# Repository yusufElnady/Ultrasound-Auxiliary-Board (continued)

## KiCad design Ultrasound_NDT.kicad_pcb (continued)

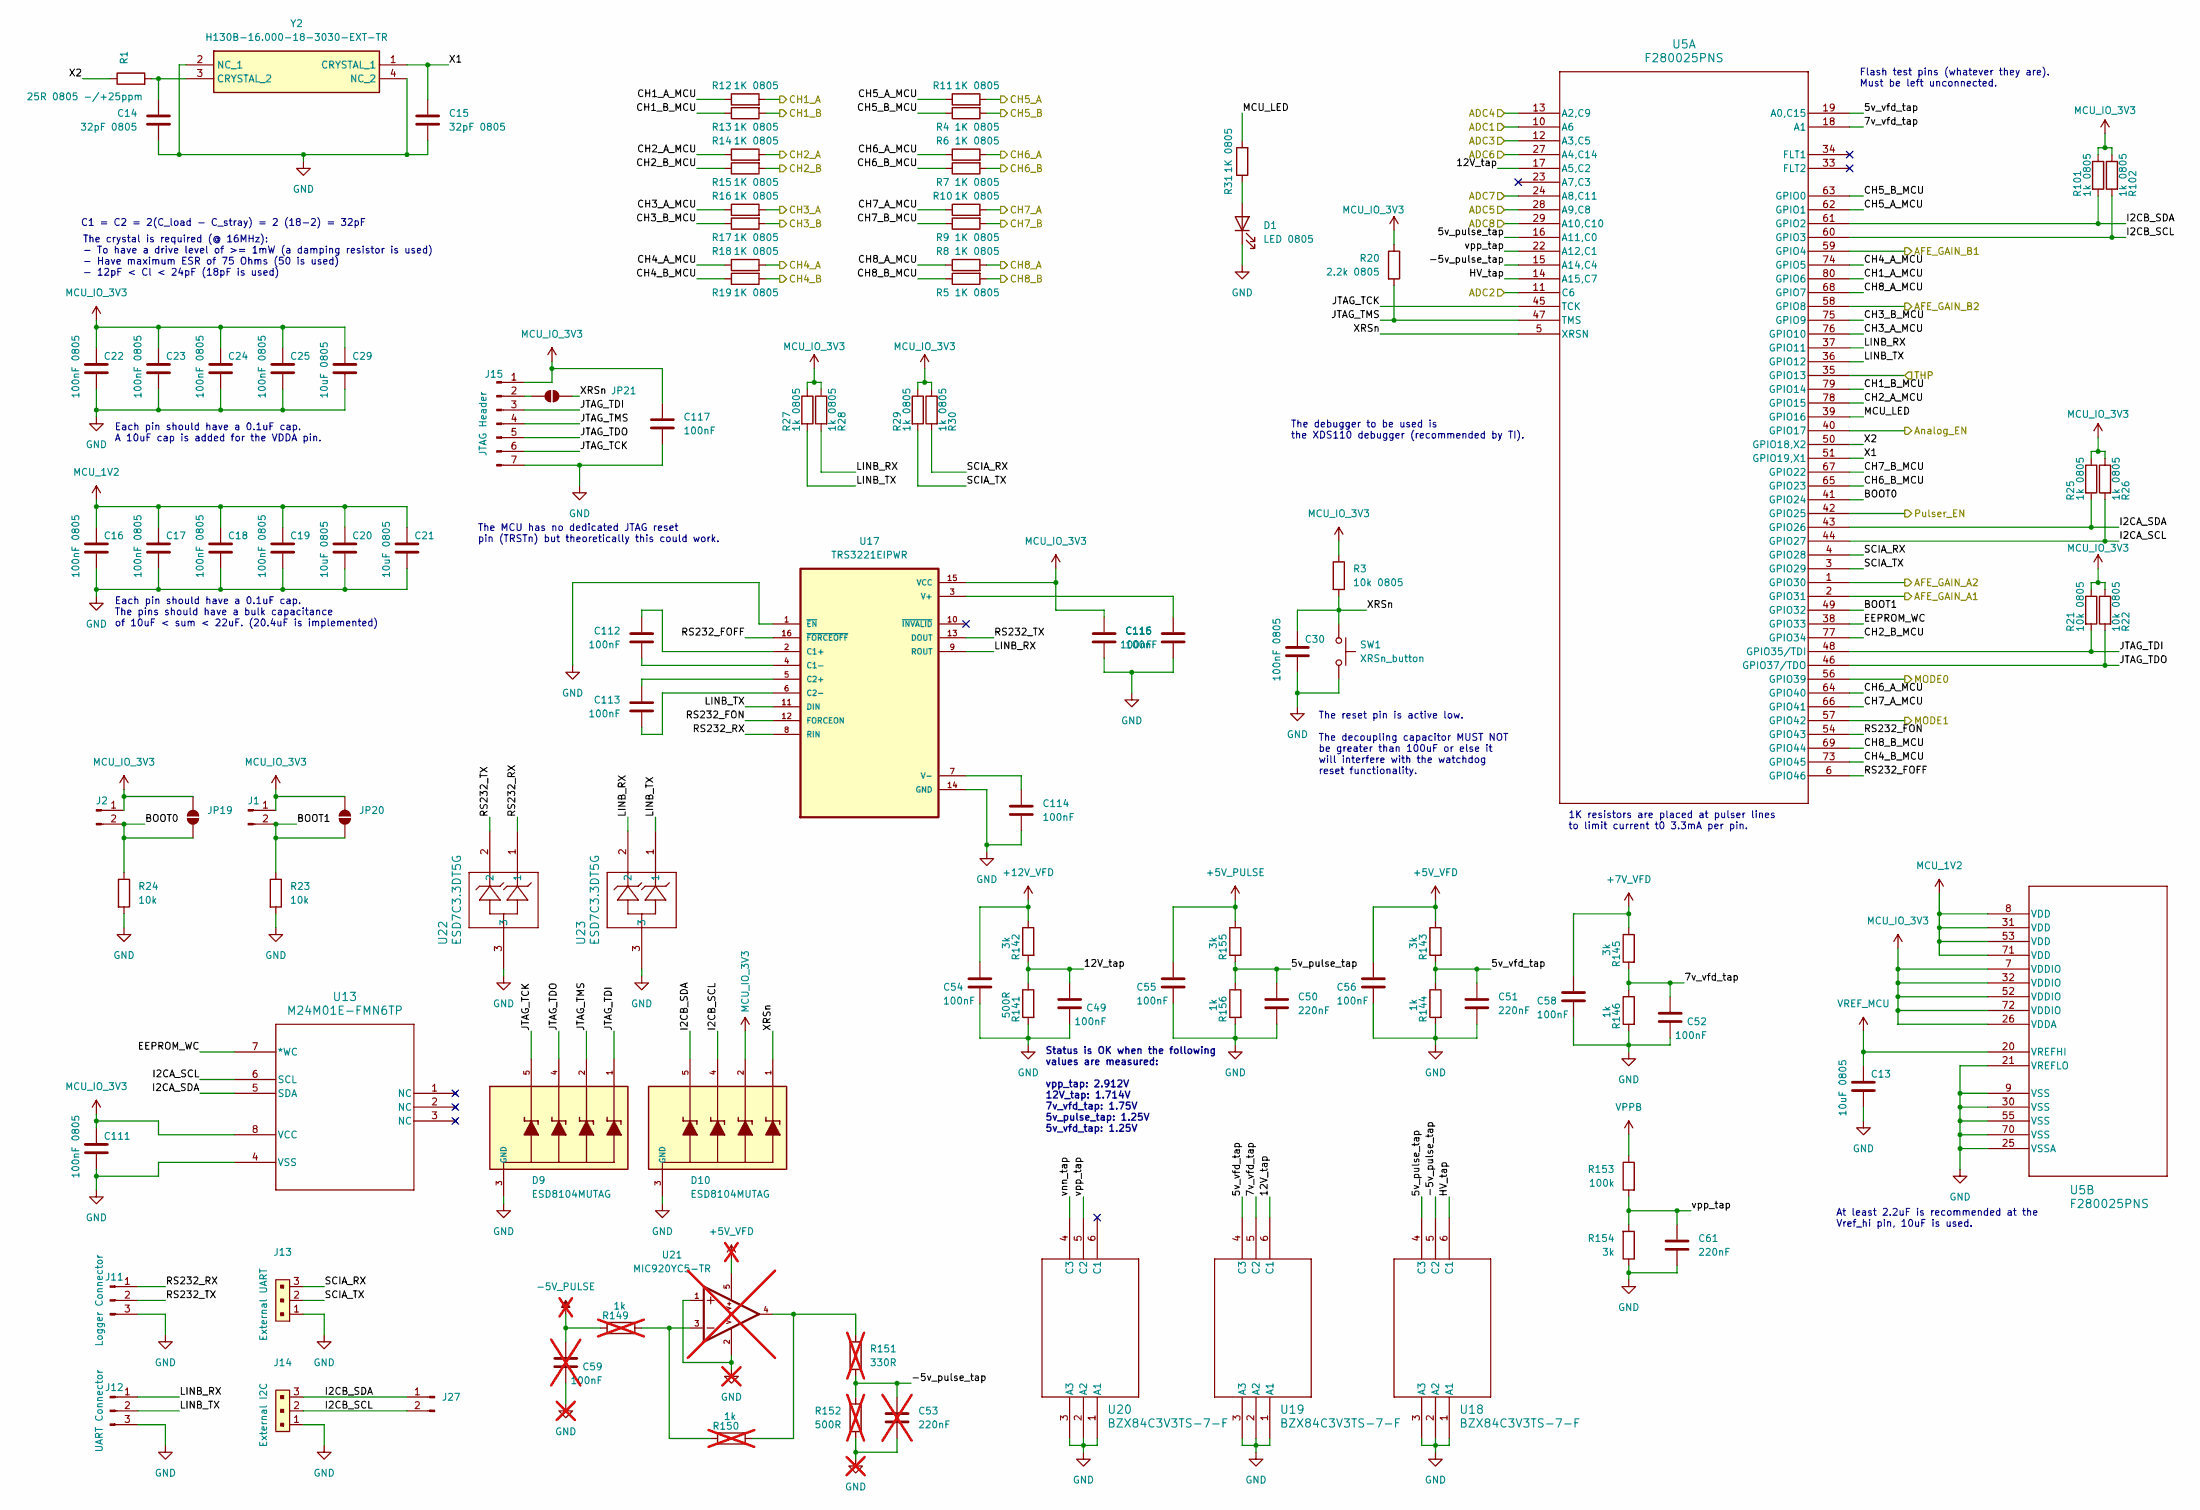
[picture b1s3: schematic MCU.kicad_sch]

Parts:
C13, C20, C21, C29: 10uF 0805; C_0603_1608Metric
C14, C15: 32pF 0805; C_0603_1608Metric
C16, C17, C18, C19, C22, C23, C24, C25, C30, C111: 100nF 0805; C_0603_1608Metric
C49, C52, C54, C55, C56, C58, C112, C113, C114, C115, C116, C117: 100nF; C_0603_1608Metric
C50, C51, C61: 220nF; C_0603_1608Metric
C53: 220nF; C_0603_1608Metric; not fitted
C59: 100nF; C_0603_1608Metric; not fitted
D1: LED 0805; LED_0805_2012Metric
D9, D10: ESD8104MUTAG; DIO_ESD8104MUTAG; PARTREV 8
J1, J2, J27: Conn_01x02_Pin; PinHeader_1x02_P2.54mm_Vertical
J11: Logger Connector; PinHeader_1x03_P2.54mm_Vertical
J12: UART Connector; PinHeader_1x03_P2.54mm_Vertical
J13: External UART; PinHeader_1x3_P2.5mm_Drill1.1mm; MPN B3B-XH-A(LF)(SN); Digi-Key_PN 455-2248-ND
J14: External I2C; PinHeader_1x3_P2.5mm_Drill1.1mm; MPN B3B-XH-A(LF)(SN); Digi-Key_PN 455-2248-ND
J15: JTAG Header; PinHeader_1x07_P2.54mm_Vertical
JP19, JP20, JP21: SolderJumper_2_Open; SolderJumper-2_P1.3mm_Open_Pad1.0x1.5mm
R1: 25R 0805 -/+25ppm; R_0603_1608Metric
R3, R21, R22: 10k 0805; R_0603_1608Metric
R4, R5, R6, R7, R8, R9, R10, R11, R12, R13, R14, R15, R16, R17, R18, R19, R31: 1K 0805; R_0603_1608Metric
R20: 2.2k 0805; R_0603_1608Metric
R23, R24: 10k; R_0603_1608Metric
R25, R26, R27, R28, R29, R30, R101, R102: 1k 0805; R_0603_1608Metric
R141: 500R; R_0603_1608Metric
R142, R143, R145, R154, R155: 3k; R_0603_1608Metric
R144, R146, R156: 1k; R_0603_1608Metric
R149, R150: 1k; R_0603_1608Metric; not fitted
R151: 330R; R_0603_1608Metric; not fitted
R152: 500R; R_0603_1608Metric; not fitted
R153: 100k; R_0603_1608Metric
SW1: XRSn_button; SW_Push_SPST_NO_Alps_SKRK
U5: F280025PNS; PQFP_025PNSR_TEX
U13: M24M01E-FMN6TP; SO8N_4X5X1P27_STM
U17: TRS3221EIPWR; SOP65P640X120-16N
U18, U19, U20: BZX84C3V3TS-7-F; SOT-363_DIO
U21: MIC920YC5-TR; SOT65P210X110-5N; PARTREV March 2006; not fitted
U22, U23: ESD7C3.3DT5G; SOT_C3.3DT5G_ONS
Y2: H130B-16.000-18-3030-EXT-TR; H130B16000183030EXTTR; Manufacturer_Part_Number H130B-16.000-18-3030-EXT-TR

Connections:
+5V_PULSE: C55.1, R155.1; also elsewhere on the board
+5V_VFD: C56.1, R143.1, U21.5; also elsewhere on the board
+7V_VFD: C58.1, R145.1; also elsewhere on the board
+12V_VFD: C54.1, R142.1; also elsewhere on the board
/Main MCU Section/5v_pulse_tap: C50.1, R155.2, R156.1, U5.16 (A11,C0), U18.4 (C3)
/Main MCU Section/5v_vfd_tap: C51.1, R143.2, R144.1, U5.19 (A0,C15), U19.4 (C3)
/Main MCU Section/7v_vfd_tap: C52.1, R145.2, R146.1, U5.18 (A1), U19.5 (C2)
/Main MCU Section/12V_tap: C49.1, R141.1, R142.2, U5.17 (A5,C2), U19.6 (C1)
/Main MCU Section/-5v_pulse_tap: C53.1, R151.1, R152.2, U5.15 (A14,C4), U18.5 (C2)
/Main MCU Section/ADC1: U5.10 (A6); also elsewhere on the board
/Main MCU Section/ADC2: U5.11 (C6); also elsewhere on the board
/Main MCU Section/ADC3: U5.12 (A3,C5); also elsewhere on the board
/Main MCU Section/ADC4: U5.13 (A2,C9); also elsewhere on the board
/Main MCU Section/ADC5: U5.28 (A9,C8); also elsewhere on the board
/Main MCU Section/ADC6: U5.27 (A4,C14); also elsewhere on the board
/Main MCU Section/ADC7: U5.24 (A8,C11); also elsewhere on the board
/Main MCU Section/ADC8: U5.29 (A10,C10); also elsewhere on the board
/Main MCU Section/AFE_GAIN_A1: U5.2 (GPIO31); also elsewhere on the board
/Main MCU Section/AFE_GAIN_A2: U5.1 (GPIO30); also elsewhere on the board
/Main MCU Section/AFE_GAIN_B1: U5.59 (GPIO4); also elsewhere on the board
/Main MCU Section/AFE_GAIN_B2: U5.58 (GPIO8); also elsewhere on the board
/Main MCU Section/Analog_EN: U5.40 (GPIO17); also elsewhere on the board
/Main MCU Section/BOOT0: J2.2, JP19.1 (A), R24.1, U5.41 (GPIO24)
/Main MCU Section/BOOT1: J1.2, JP20.1 (A), R23.1, U5.49 (GPIO32)
/Main MCU Section/CH1_A: R12.2; also elsewhere on the board
/Main MCU Section/CH1_A_MCU: R12.1, U5.80 (GPIO6)
/Main MCU Section/CH1_B: R13.2; also elsewhere on the board
/Main MCU Section/CH1_B_MCU: R13.1, U5.79 (GPIO14)
/Main MCU Section/CH2_A: R14.2; also elsewhere on the board
/Main MCU Section/CH2_A_MCU: R14.1, U5.78 (GPIO15)
/Main MCU Section/CH2_B: R15.2; also elsewhere on the board
/Main MCU Section/CH2_B_MCU: R15.1, U5.77 (GPIO34)
/Main MCU Section/CH3_A: R16.2; also elsewhere on the board
/Main MCU Section/CH3_A_MCU: R16.1, U5.76 (GPIO10)
/Main MCU Section/CH3_B: R17.2; also elsewhere on the board
/Main MCU Section/CH3_B_MCU: R17.1, U5.75 (GPIO9)
/Main MCU Section/CH4_A: R18.2; also elsewhere on the board
/Main MCU Section/CH4_A_MCU: R18.1, U5.74 (GPIO5)
/Main MCU Section/CH4_B: R19.2; also elsewhere on the board
/Main MCU Section/CH4_B_MCU: R19.1, U5.73 (GPIO45)
/Main MCU Section/CH5_A: R11.2; also elsewhere on the board
/Main MCU Section/CH5_A_MCU: R11.1, U5.62 (GPIO1)
/Main MCU Section/CH5_B: R4.2; also elsewhere on the board
/Main MCU Section/CH5_B_MCU: R4.1, U5.63 (GPIO0)
/Main MCU Section/CH6_A: R6.2; also elsewhere on the board
/Main MCU Section/CH6_A_MCU: R6.1, U5.64 (GPIO40)
/Main MCU Section/CH6_B: R7.2; also elsewhere on the board
/Main MCU Section/CH6_B_MCU: R7.1, U5.65 (GPIO23)
/Main MCU Section/CH7_A: R10.2; also elsewhere on the board
/Main MCU Section/CH7_A_MCU: R10.1, U5.66 (GPIO41)
/Main MCU Section/CH7_B: R9.2; also elsewhere on the board
/Main MCU Section/CH7_B_MCU: R9.1, U5.67 (GPIO22)
/Main MCU Section/CH8_A: R8.2; also elsewhere on the board
/Main MCU Section/CH8_A_MCU: R8.1, U5.68 (GPIO7)
/Main MCU Section/CH8_B: R5.2; also elsewhere on the board
/Main MCU Section/CH8_B_MCU: R5.1, U5.69 (GPIO44)
/Main MCU Section/EEPROM_WC: U5.38 (GPIO33), U13.7 (*WC)
/Main MCU Section/HV_tap: U5.14 (A15,C7), U18.6 (C1)
/Main MCU Section/I2CA_SCL: R26.2, U5.44 (GPIO27), U13.6 (SCL)
/Main MCU Section/I2CA_SDA: R25.2, U5.43 (GPIO26), U13.5 (SDA)
/Main MCU Section/I2CB_SCL: D10.4, J14.2, J27.2, R102.2, U5.60 (GPIO3)
/Main MCU Section/I2CB_SDA: D10.5, J14.3, J27.1, R101.2, U5.61 (GPIO2)
/Main MCU Section/JTAG_TCK: D9.5, J15.6, U5.45 (TCK)
/Main MCU Section/JTAG_TDI: D9.1, J15.3, R21.2, U5.48 (GPIO35/TDI)
/Main MCU Section/JTAG_TDO: D9.4, J15.5, R22.2, U5.46 (GPIO37/TDO)
/Main MCU Section/JTAG_TMS: D9.2, J15.4, R20.2, U5.47 (TMS)
/Main MCU Section/LINB_RX: J12.1, R28.2, U5.37 (GPIO11), U17.9 (ROUT), U23.2
/Main MCU Section/LINB_TX: J12.2, R27.2, U5.36 (GPIO12), U17.11 (DIN), U23.1
/Main MCU Section/MCU_LED: R31.2, U5.39 (GPIO16)
/Main MCU Section/MODE0: U5.56 (GPIO39); also elsewhere on the board
/Main MCU Section/MODE1: U5.57 (GPIO42); also elsewhere on the board
/Main MCU Section/Pulser_EN: U5.42 (GPIO25); also elsewhere on the board
/Main MCU Section/RS232_FOFF: U5.6 (GPIO46), U17.16 (~FORCEOFF)
/Main MCU Section/RS232_FON: U5.54 (GPIO43), U17.12 (FORCEON)
/Main MCU Section/RS232_RX: J11.1, U17.8 (RIN), U22.1
/Main MCU Section/RS232_TX: J11.2, U17.13 (DOUT), U22.2
/Main MCU Section/SCIA_RX: J13.3, R30.2, U5.4 (GPIO28)
/Main MCU Section/SCIA_TX: J13.2, R29.2, U5.3 (GPIO29)
/Main MCU Section/THP: U5.35 (GPIO13); also elsewhere on the board
/Main MCU Section/X1: C15.1, U5.51 (GPIO19,X1), Y2.1 (CRYSTAL_1)
/Main MCU Section/X2: R1.1, U5.50 (GPIO18,X2)
/Main MCU Section/XRSn: C30.1, D10.1, JP21.2 (B), R3.2, SW1.1, U5.5 (XRSN)
/Main MCU Section/vnn_tap: U20.4 (C3)
/Main MCU Section/vpp_tap: C61.1, R153.2, R154.2, U5.22 (A12,C1), U20.5 (C2)
GND: C13.2, C14.2, C15.2, C16.2, C17.2, C18.2, C19.2, C20.2, C21.2, C22.2, C23.2, C24.2, C25.2, C29.2, C30.2, C49.2, C50.2, C51.2, C52.2, C53.2, C54.2, C55.2, C56.2, C58.2, C59.2, C61.2, C111.2, C114.2, C115.2, C116.2, C117.2, D1.1 (K), D9.3 (GND), D9.8 (GND), D10.3 (GND), D10.8 (GND), J11.3, J12.3, J13.1, J14.1, J15.7, R23.2, R24.2, R141.2, R144.2, R146.2, R152.1, R154.1, R156.2, SW1.2, U5.9 (VSS), U5.21 (VREFLO), U5.25 (VSSA), U5.30 (VSS), U5.55 (VSS), U5.70 (VSS), U13.4 (VSS), U17.1 (~EN), U17.14 (GND), U18.1 (A1), U18.2 (A2), U18.3 (A3), U19.1 (A1), U19.2 (A2), U19.3 (A3), U20.1 (A1), U20.2 (A2), U20.3 (A3), U21.1, U21.2, U22.3, U23.3, Y2.2 (NC_1), Y2.4 (NC_2); also elsewhere on the board
MCU_1V2: C16.1, C17.1, C18.1, C19.1, C20.1, C21.1, U5.8 (VDD), U5.31 (VDD), U5.53 (VDD), U5.71 (VDD)
MCU_IO_3V3: C22.1, C23.1, C24.1, C25.1, C29.1, C111.1, C116.1, C117.1, D10.2, J1.1, J2.1, J15.1, JP19.2 (B), JP20.2 (B), R3.1, R20.1, R21.1, R22.1, R25.1, R26.1, R27.1, R28.1, R29.1, R30.1, R101.1, R102.1, U5.7 (VDDIO), U5.26 (VDDA), U5.32 (VDDIO), U5.52 (VDDIO), U5.72 (VDDIO), U13.8 (VCC), U17.15 (VCC); also elsewhere on the board
unnamed: C59.1, R149.2
unnamed: D1.2 (A), R31.1
unnamed: J15.2, JP21.1 (A)
unnamed: R149.1, R150.2, U21.3
unnamed: R150.1, R151.2, U21.4
unnamed: C112.1, U17.2 (C1+)
unnamed: C112.2, U17.4 (C1-)
unnamed: C113.1, U17.5 (C2+)
unnamed: C113.2, U17.6 (C2-)
unnamed: C115.1, U17.3 (V+)
unnamed: C114.1, U17.7 (V-)
unnamed: C14.1, R1.2, Y2.3 (CRYSTAL_2)
VPPB: R153.1; also elsewhere on the board
VREF_MCU: C13.1, U5.20 (VREFHI); also elsewhere on the board

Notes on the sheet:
Status is OK when the following values are measured: vpp_tap: 2.912V 12V_tap: 1.714V 7v_vfd_tap: 1.75V 5v_pulse_tap: 1.25V 5v_vfd_tap: 1.25V
The crystal is required (@ 16MHz): - To have a drive level of >= 1mW (a damping resistor is used) - Have maximum ESR of 75 Ohms (50 is used) - 12pF < Cl < 24pF (18pF is used)
Each pin should have a 0.1uF cap. The pins should have a bulk capacitance of 10uF < sum < 22uF. (20.4uF is implemented)
Each pin should have a 0.1uF cap. A 10uF cap is added for the VDDA pin.
The debugger to be used is the XDS110 debugger (recommended by TI).
The MCU has no dedicated JTAG reset pin (TRSTn) but theoretically this could work.
At least 2.2uF is recommended at the Vref_hi pin, 10uF is used.
1K resistors are placed at pulser lines to limit current t0 3.3mA per pin.
The reset pin is active low. The decoupling capacitor MUST NOT be greater than 100uF or else it will interfere with the watchdog reset functionality.
Flash test pins (whatever they are). Must be left unconnected.
C1 = C2 = 2(C_load - C_stray) = 2 (18-2) = 32pF

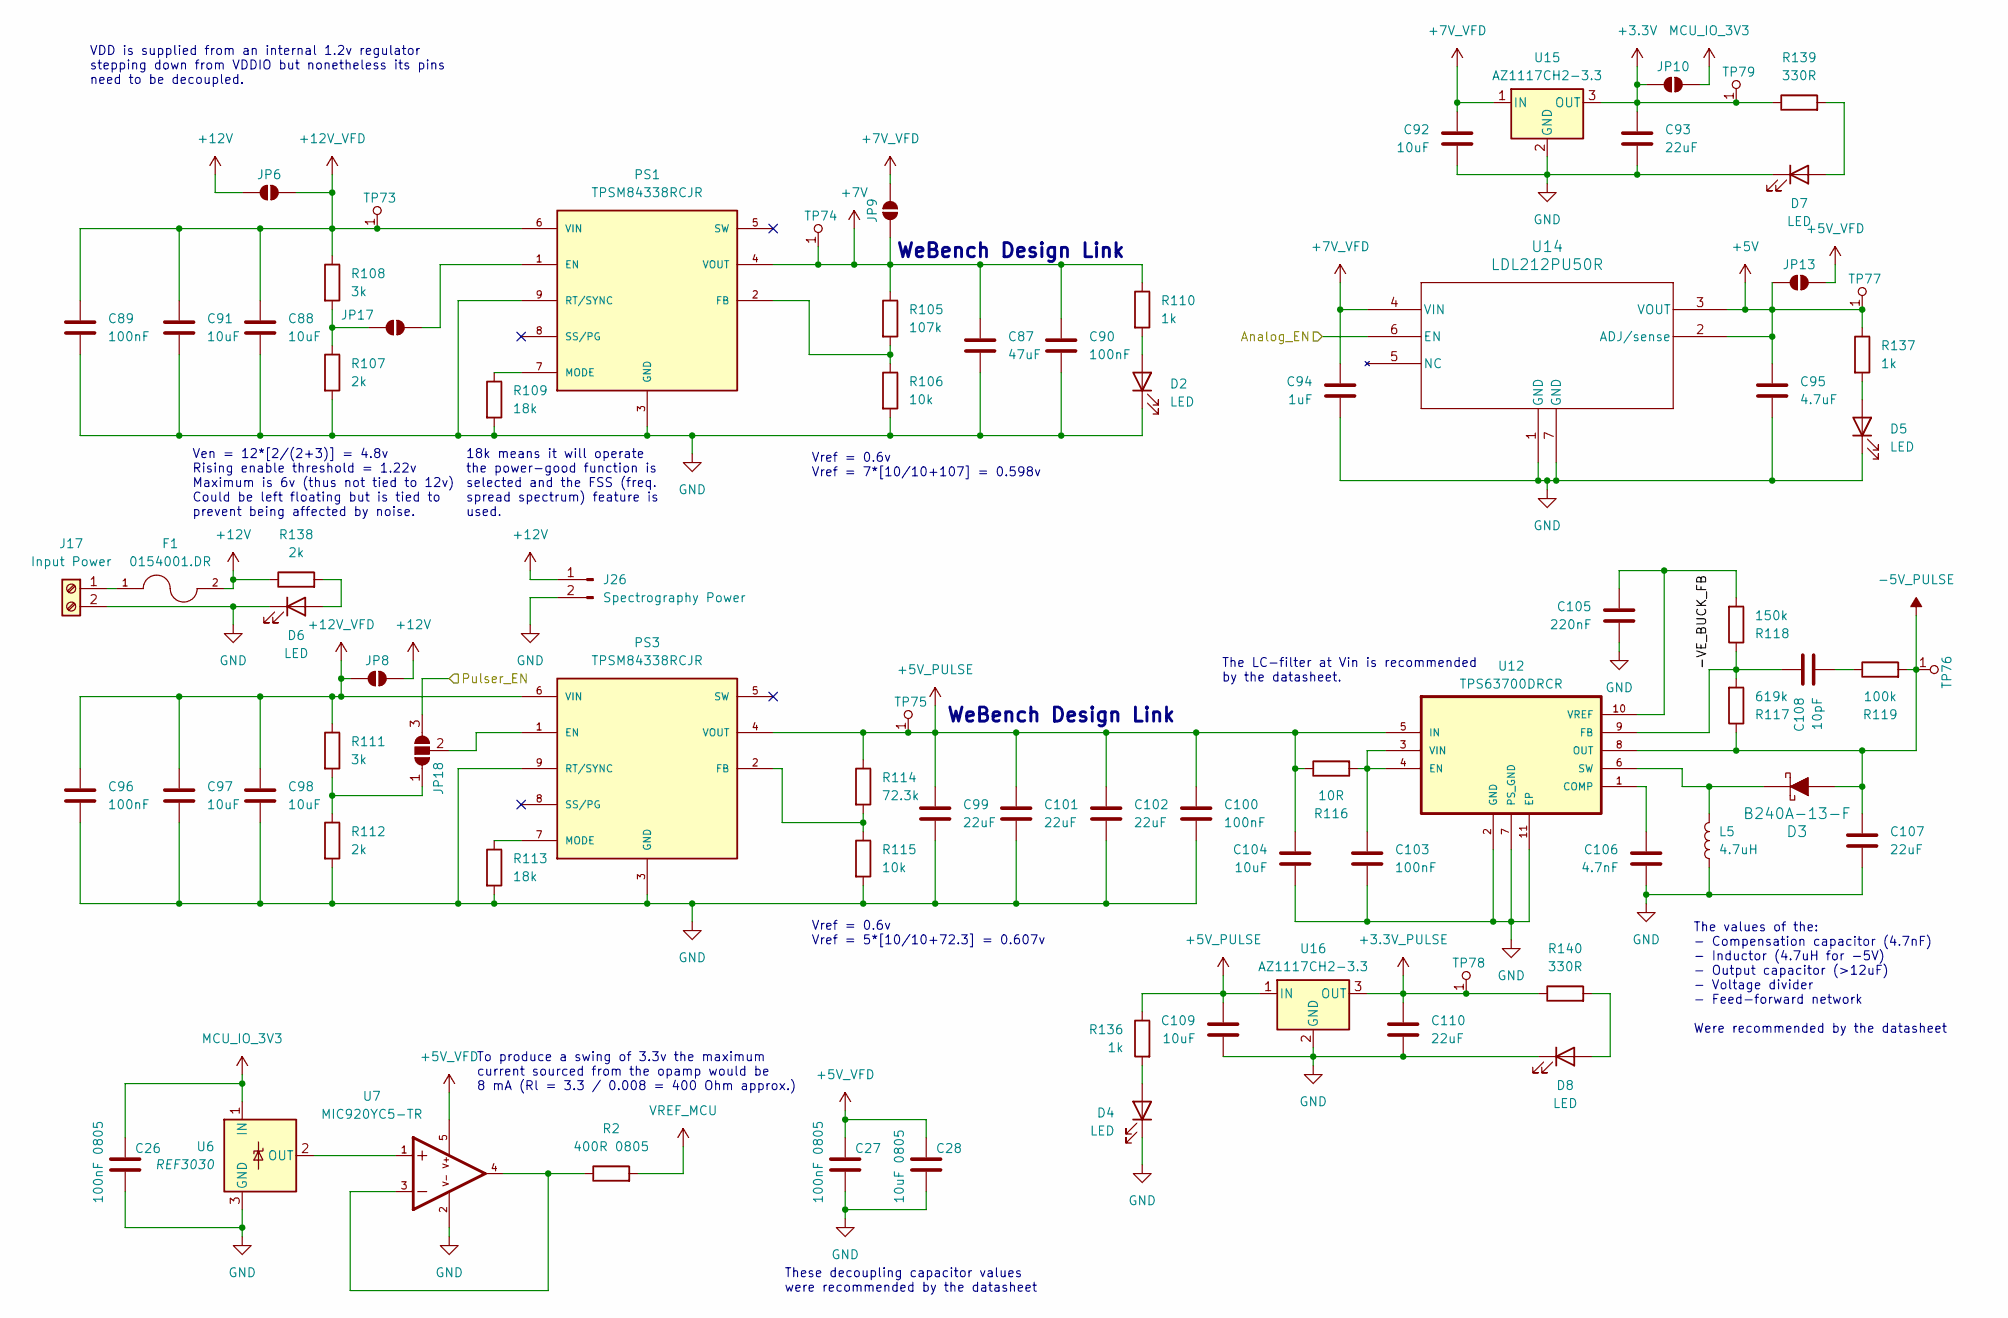
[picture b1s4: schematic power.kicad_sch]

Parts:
C26, C27: 100nF 0805; C_0603_1608Metric
C28: 10uF 0805; C_0603_1608Metric
C87: 47uF; C_1210_3225Metric
C88, C91, C92, C97, C98, C104, C109: 10uF; C_0805_2012Metric
C89, C90, C96, C100, C103: 100nF; C_0603_1608Metric
C93, C99, C101, C102, C107, C110: 22uF; C_0805_2012Metric
C94: 1uF; C_0603_1608Metric
C95: 4.7uF; C_0805_2012Metric
C105: 220nF; C_0603_1608Metric
C106: 4.7nF; C_0603_1608Metric
C108: 10pF; C_0603_1608Metric
D2, D4, D5, D6, D7, D8: LED; LED_0805_2012Metric
D3: B240A-13-F; DO-214AC; MPN B240A-13-F; Digi-Key_PN B240A-FDICT-ND
F1: 0154001.DR; FUSE_0154001.DR; PARTREV GD
J17: Input Power; TerminalBlock_MaiXu_MX126-5.0-02P_1x02_P5.00mm
J26: Spectrography Power; PinHeader_1x02_P2.54mm_Vertical
JP6, JP8, JP9, JP10, JP13: SolderJumper_2_Open; SolderJumper-2_P1.3mm_Open_RoundedPad1.0x1.5mm
JP17: SolderJumper_2_Open; SolderJumper-2_P1.3mm_Open_Pad1.0x1.5mm
JP18: SolderJumper_3_Open; SolderJumper-3_P1.3mm_Open_Pad1.0x1.5mm
L5: 4.7uH; L_0805_2012Metric
PS1, PS3: TPSM84338RCJR; CONV_TPSM84338RCJR; PARTREV November 2024
R2: 400R 0805; R_0603_1608Metric
R105: 107k; R_0603_1608Metric
R106, R115: 10k; R_0603_1608Metric
R107, R112, R138: 2k; R_0603_1608Metric
R108, R111: 3k; R_0603_1608Metric
R109, R113: 18k; R_0603_1608Metric
R110, R136, R137: 1k; R_0603_1608Metric
R114: 72.3k; R_0603_1608Metric
R116: 10R; R_0603_1608Metric
R117: 619k; R_0603_1608Metric
R118: 150k; R_0603_1608Metric
R119: 100k; R_0603_1608Metric
R139, R140: 330R; R_0603_1608Metric
TP73, TP74, TP75, TP76, TP77, TP78, TP79: RCT-0C; PROBE_PAD_0805; MPN RCT-0C; Digi-Key_PN A106144CT-ND
U6: REF3030; SOT-23
U7: MIC920YC5-TR; SOT65P210X110-5N; PARTREV March 2006
U12: TPS63700DRCR; VREG_V62_16624-01YE
U14: LDL212PU50R; DFN_2PU50R_STM
U15, U16: AZ1117CH2-3.3; SOT-223-3_TabPin2

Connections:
+3.3V: C93.1, JP10.1 (A), R139.1, TP79.1, U15.3 (OUT)
+3.3V_PULSE: C110.1, R140.1, TP78.1, U16.3 (OUT); also elsewhere on the board
+5V: C95.1, JP13.1 (A), R137.1, TP77.1, U14.2 (ADJ/sense), U14.3 (VOUT)
+5V_PULSE: C99.1, C100.1, C101.1, C102.1, C104.1, C109.1, PS3.4 (VOUT), R114.1, R116.1, R136.1, TP75.1, U12.5 (IN), U16.1 (IN); also elsewhere on the board
+5V_VFD: C27.1, C28.1, JP13.2 (B), U7.5; also elsewhere on the board
+7V: C87.1, C90.1, JP9.1 (A), PS1.4 (VOUT), R105.1, R110.1, TP74.1
+7V_VFD: C92.1, C94.1, JP9.2 (B), U14.4 (VIN), U15.1 (IN); also elsewhere on the board
+12V: F1.2, J26.1, JP6.1 (A), JP8.2 (B), R138.1
+12V_VFD: C88.1, C89.1, C91.1, C96.1, C97.1, C98.1, JP6.2 (B), JP8.1 (A), PS1.6 (VIN), PS3.6 (VIN), R108.1, R111.1, TP73.1; also elsewhere on the board
-5V_PULSE: C107.1, D3.A, R117.1, R119.2, TP76.1, U12.8 (OUT); also elsewhere on the board
/Main MCU Section/Analog_EN: U14.6 (EN); also elsewhere on the board
/Main MCU Section/Pulser_EN: JP18.3 (B); also elsewhere on the board
/Power Section/-VE_BUCK_FB: C108.1, R117.2, R118.1, U12.9 (FB)
GND: C26.2, C27.2, C28.2, C87.2, C88.2, C89.2, C90.2, C91.2, C92.2, C93.2, C94.2, C95.2, C96.2, C97.2, C98.2, C99.2, C100.2, C101.2, C102.2, C103.2, C104.2, C105.2, C106.2, C107.2, C109.2, C110.2, D2.1 (K), D4.1 (K), D5.1 (K), D6.1 (K), D7.1 (K), D8.1 (K), J17.2, J26.2, L5.1, PS1.3 (GND), PS1.9 (RT/SYNC), PS3.3 (GND), PS3.9 (RT/SYNC), R106.2, R107.2, R109.2, R112.2, R113.2, R115.2, U6.3 (GND), U7.2, U12.2 (GND), U12.7 (PS_GND), U12.11 (EP), U14.1 (GND), U14.7 (GND), U15.2 (GND), U16.2 (GND); also elsewhere on the board
MCU_IO_3V3: C26.1, JP10.2 (B), U6.1 (IN); also elsewhere on the board
unnamed: C108.2, R119.1
unnamed: D2.2 (A), R110.2
unnamed: D4.2 (A), R136.2
unnamed: D5.2 (A), R137.2
unnamed: D6.2 (A), R138.2
unnamed: D7.2 (A), R139.2
unnamed: D8.2 (A), R140.2
unnamed: F1.1, J17.1
unnamed: JP17.1 (A), R107.1, R108.2
unnamed: JP17.2 (B), PS1.1 (EN)
unnamed: JP18.1 (A), R111.2, R112.1
unnamed: JP18.2 (C), PS3.1 (EN)
unnamed: PS1.2 (FB), R105.2, R106.1
unnamed: PS1.7 (MODE), R109.1
unnamed: PS3.2 (FB), R114.2, R115.1
unnamed: PS3.7 (MODE), R113.1
unnamed: R2.1, U7.3, U7.4
unnamed: U6.2 (OUT), U7.1
unnamed: C106.1, U12.1 (COMP)
unnamed: C103.1, R116.2, U12.3 (VIN), U12.4 (EN)
unnamed: D3.K, L5.2, U12.6 (SW)
unnamed: C105.1, R118.2, U12.10 (VREF)
VREF_MCU: R2.2; also elsewhere on the board

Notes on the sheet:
Vref = 0.6v Vref = 7*[10/10+107] = 0.598v
18k means it will operate the power-good function is selected and the FSS (freq. spread spectrum) feature is used.
WeBench Design Link
VDD is supplied from an internal 1.2v regulator stepping down from VDDIO but nonetheless its pins need to be decoupled.
Vref = 0.6v Vref = 5*[10/10+72.3] = 0.607v
The values of the: - Compensation capacitor (4.7nF) - Inductor (4.7uH for -5V) - Output capacitor (>12uF) - Voltage divider - Feed-forward network Were recommended by the datasheet
To produce a swing of 3.3v the maximum current sourced from the opamp would be 8 mA (Rl = 3.3 / 0.008 = 400 Ohm approx.)
Ven = 12*[2/(2+3)] = 4.8v Rising enable threshold = 1.22v Maximum is 6v (thus not tied to 12v) Could be left floating but is tied to prevent being affected by noise.
The LC-filter at Vin is recommended by the datasheet.
These decoupling capacitor values were recommended by the datasheet

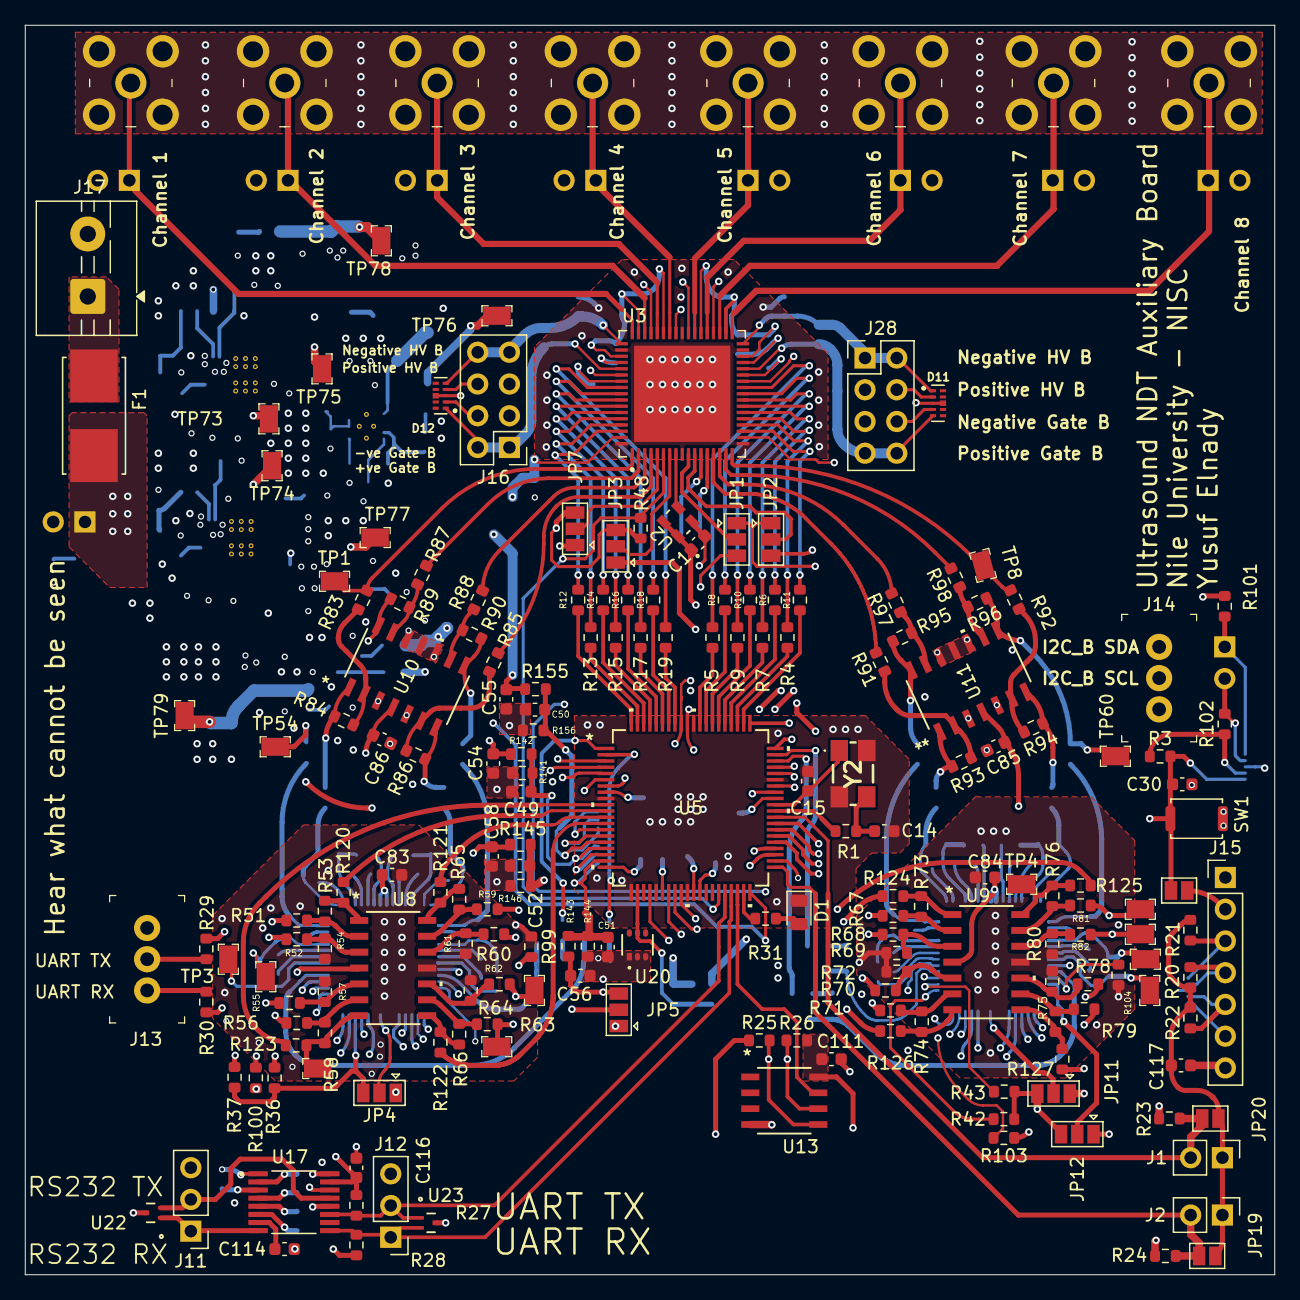
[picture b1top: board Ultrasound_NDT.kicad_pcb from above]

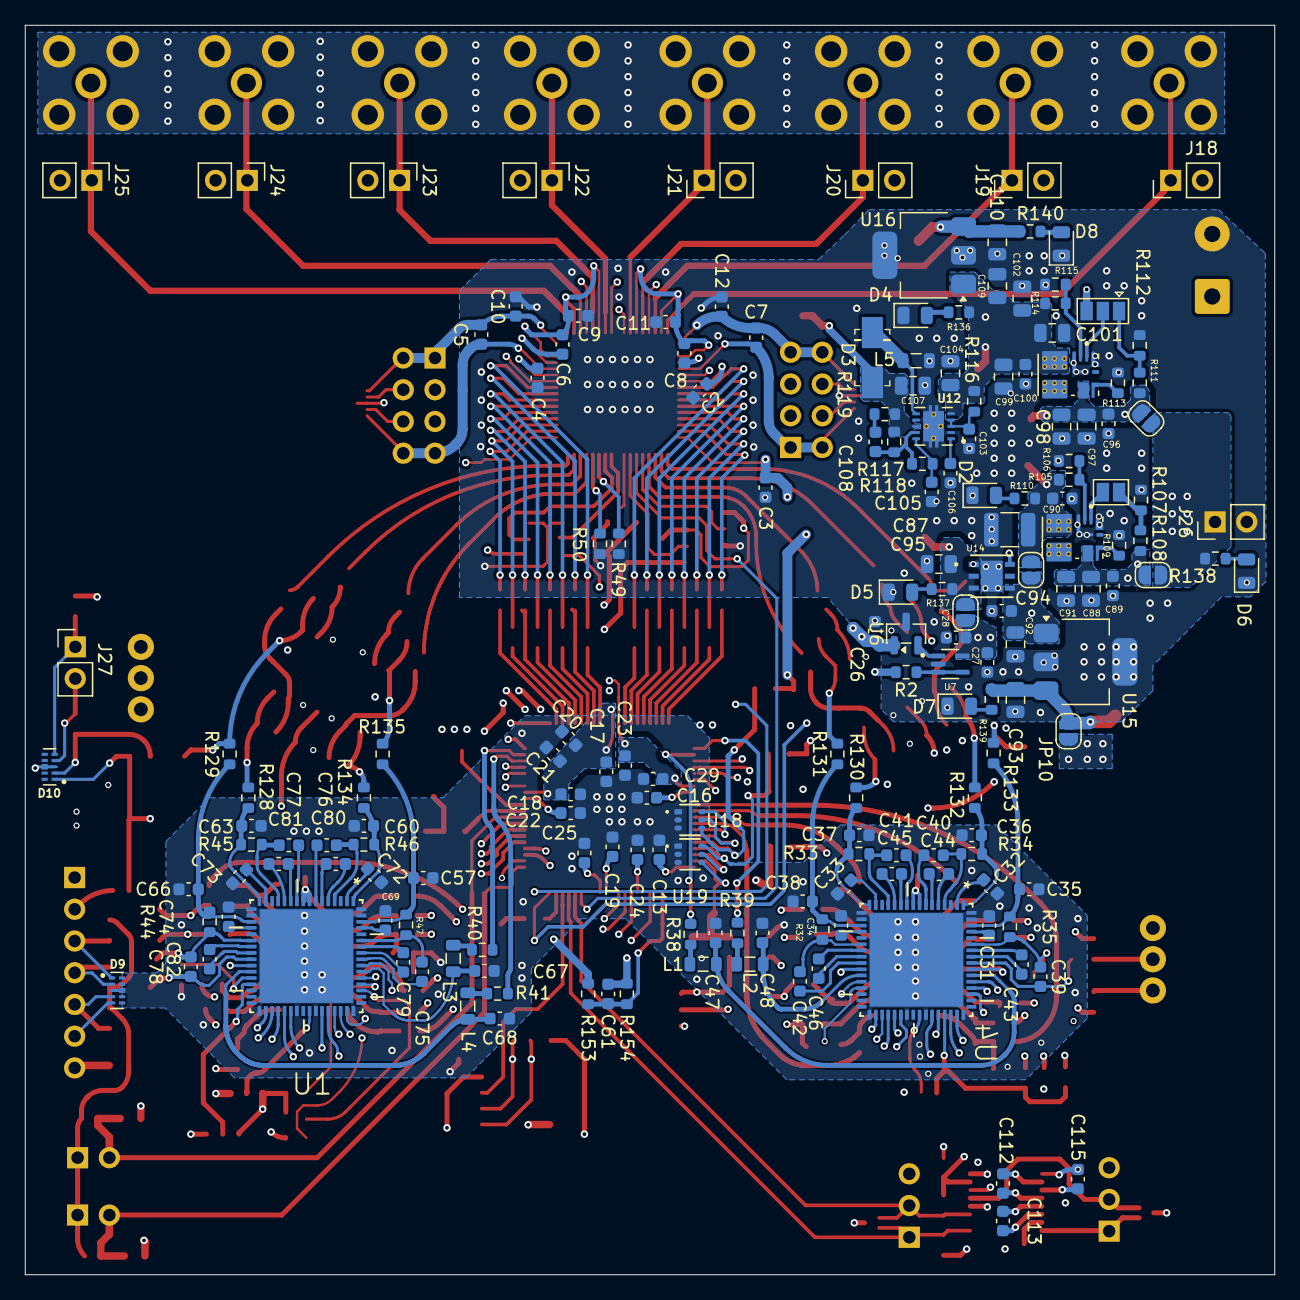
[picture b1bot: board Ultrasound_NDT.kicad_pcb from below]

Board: 6 copper layers, 100.0 x 100.0 mm, 371 parts (178 on the bottom side), 278 nets.

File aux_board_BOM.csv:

Reference|Qty|Value|DNP|Exclude from BOM|Exclude from Board|Footprint|MANUFACTURER|Description
C1,C13,C20,C21,C28,C29|6|10uF 0805||||Capacitor_SMD:C_0603_1608Metric||Unpolarized capacitor
C2,C3,C4,C9,C10,C11,C12,C16,C17,C18,C19,C22,C23,C24,C25,C26,C27,C30,C31,C32,C33,C34,C39,C40,C41,C42,C43,C44,C45,C46,C69,C72,C73,C74,C75,C76,C77,C78,C79,C80,C81,C82,C83,C84,C85,C86,C111|47|100nF 0805||||Capacitor_SMD:C_0603_1608Metric||Unpolarized capacitor
C5,C6,C7,C8|4|1uF 0805 10v||||Capacitor_SMD:C_0603_1608Metric||Unpolarized capacitor
C14,C15|2|32pF 0805||||Capacitor_SMD:C_0603_1608Metric||Unpolarized capacitor
C35,C36,C37,C38,C57,C60,C63,C66|8|22pF 0805||||Capacitor_SMD:C_0603_1608Metric||Unpolarized capacitor
C47,C48,C67,C68|4|22nF 0805||||Capacitor_SMD:C_0603_1608Metric||Unpolarized capacitor
C49,C52,C54,C55,C56,C58,C89,C90,C96,C100,C103,C112,C113,C114,C115,C116,C117|17|100nF||||Capacitor_SMD:C_0603_1608Metric||100nF 50v 0603,100nF 50v 0805
C50,C51,C61,C105|4|220nF||||Capacitor_SMD:C_0603_1608Metric||220nF 0603,220nF 50v 0805
C87|1|47uF||||Capacitor_SMD:C_1210_3225Metric||47uF >10v 1210
C88,C91,C92,C97,C98,C104,C109|7|10uF||||Capacitor_SMD:C_0805_2012Metric||10uF 0805,10uF 50v 0805,10uF >10v 0805
C93,C99,C101,C102,C107,C110|6|22uF||||Capacitor_SMD:C_0805_2012Metric||22uF 0805,22uF >10v 0805
C94|1|1uF||||Capacitor_SMD:C_0603_1608Metric||1uF 0805
C95|1|4.7uF||||Capacitor_SMD:C_0805_2012Metric||4.7uF 0805
C106|1|4.7nF||||Capacitor_SMD:C_0603_1608Metric||4.7nF 50v 0805
C108|1|10pF||||Capacitor_SMD:C_0603_1608Metric||10pF 0805
D1|1|LED 0805||||LED_SMD:LED_0805_2012Metric||Light emitting diode
D2,D4,D5,D6,D7,D8|6|LED||||LED_SMD:LED_0805_2012Metric||Light emitting diode
D3|1|B240A-13-F||||digikey-footprints:DO-214AC||DIODE SCHOTTKY 40V 2A SMA
D9,D10,D11,D12|4|ESD8104MUTAG||||ESD8104MUTAG:DIO_ESD8104MUTAG|ON Semiconductor|
F1|1|0154001.DR||||0154001.DR:FUSE_0154001.DR|Littelfuse|
J1,J2,J18,J19,J20,J21,J22,J23,J24,J25,J27|11|Conn_01x02_Pin||||Connector_PinHeader_2.54mm:PinHeader_1x02_P2.54mm_Vertical||Generic connector, single row, 01x02, script generated
J3,J4,J5,J6,J7,J8,J9,J10|8|CONSMA002-SMD||||CONSMA002-SMD:TE_CONSMA002-SMD|TE Connectivity|
J11|1|Logger Connector||||Connector_PinHeader_2.54mm:PinHeader_1x03_P2.54mm_Vertical||Generic connector, single row, 01x03, script generated
J12|1|UART Connector||||Connector_PinHeader_2.54mm:PinHeader_1x03_P2.54mm_Vertical||Generic connector, single row, 01x03, script generated
J13|1|External UART||||digikey-footprints:PinHeader_1x3_P2.5mm_Drill1.1mm||CONN HEADER VERT 3POS 2.5MM
J14|1|External I2C||||digikey-footprints:PinHeader_1x3_P2.5mm_Drill1.1mm||CONN HEADER VERT 3POS 2.5MM
J15|1|JTAG Header||||Connector_PinHeader_2.54mm:PinHeader_1x07_P2.54mm_Vertical||Generic connector, single row, 01x07, script generated
J16,J28|2|Conn_02x04_Odd_Even||||Connector_PinHeader_2.54mm:PinHeader_2x04_P2.54mm_Vertical||Generic connector, double row, 02x04, odd/even pin numbering scheme (row 1 odd numbers, row 2 even numbers), script generated (kicad-library-utils/schlib/autogen/connector/)
J17|1|Input Power||||TerminalBlock:TerminalBlock_MaiXu_MX126-5.0-02P_1x02_P5.00mm||Generic screw terminal, single row, 01x02, script generated (kicad-library-utils/schlib/autogen/connector/)
J26|1|Spectrography Power||||Connector_PinHeader_2.54mm:PinHeader_1x02_P2.54mm_Vertical||Generic connector, single row, 01x02, script generated
JP1,JP2,JP3,JP4,JP5,JP7,JP11,JP12,JP18|9|SolderJumper_3_Open||Excluded from BOM||Jumper:SolderJumper-3_P1.3mm_Open_Pad1.0x1.5mm||Solder Jumper, 3-pole, open
JP6,JP8,JP9,JP10,JP13|5|SolderJumper_2_Open||Excluded from BOM||Jumper:SolderJumper-2_P1.3mm_Open_RoundedPad1.0x1.5mm||Solder Jumper, 2-pole, open
JP17,JP19,JP20,JP21|4|SolderJumper_2_Open||Excluded from BOM||Jumper:SolderJumper-2_P1.3mm_Open_Pad1.0x1.5mm||Solder Jumper, 2-pole, open
L1,L2,L3,L4|4|100uH 0805||||Inductor_SMD:L_0805_2012Metric||Inductor
L5|1|4.7uH||||Inductor_SMD:L_0805_2012Metric||4.7uH 0805 (MLZ2012N4R7LT000)
PS1,PS3|2|TPSM84338RCJR||||TPSM84338RCJR:CONV_TPSM84338RCJR|Texas Instruments|
R1|1|25R 0805 -/+25ppm||||Resistor_SMD:R_0603_1608Metric||Resistor
R2|1|400R 0805||||Resistor_SMD:R_0603_1608Metric||Resistor
R3,R21,R22,R49,R50|5|10k 0805||||Resistor_SMD:R_0603_1608Metric||Resistor
R4,R5,R6,R7,R8,R9,R10,R11,R12,R13,R14,R15,R16,R17,R18,R19,R31|17|1K 0805||||Resistor_SMD:R_0603_1608Metric||Resistor
R20|1|2.2k 0805||||Resistor_SMD:R_0603_1608Metric||Resistor
R23,R24,R106,R115|4|10k||||Resistor_SMD:R_0603_1608Metric||10k 0.1% 25ppm 0805,10k 0603,Resistor
R25,R26,R27,R28,R29,R30,R48,R101,R102|9|1k 0805||||Resistor_SMD:R_0603_1608Metric||Resistor
R32,R33,R34,R35,R44,R45,R46,R47|8|280R 0805||||Resistor_SMD:R_0603_1608Metric||Resistor
R36,R37,R42,R43|4|500R 0805||||Resistor_SMD:R_0603_1608Metric||Resistor
R38,R40,R41,R120,R121,R122,R123,R124,R125,R126,R127,R128,R129,R130,R131,R132,R133,R134,R135|19|90R 0805||||Resistor_SMD:R_0603_1608Metric||Resistor
R39|1|90R 0806||||Resistor_SMD:R_0603_1608Metric||Resistor
R51,R52,R55,R56,R59,R60,R62,R63,R67,R68,R70,R71,R78,R79,R81,R82|16|2.7k||||Resistor_SMD:R_0603_1608Metric||2.7k 0805 0.1%
R53,R54,R57,R58,R61,R64,R65,R66,R69,R72,R73,R74,R75,R76,R77,R80|16|3.9k||||Resistor_SMD:R_0603_1608Metric||3.9k 0805 0.1%
R83,R85,R87,R88,R91,R92,R97,R98,R110,R136,R137,R144,R146,R156|14|1k||||Resistor_SMD:R_0603_1608Metric||1k 0.1% 25ppm 0805,1k 0805 0.1%
R84,R86,R89,R90,R93,R94,R95,R96|8|220R||||Resistor_SMD:R_0603_1608Metric||220R 0805 0.1%
R99,R100,R103,R104|4|3.5k||||Resistor_SMD:R_0603_1608Metric||3.5k 0805 0.1%
R105|1|107k||||Resistor_SMD:R_0603_1608Metric||107k 0.1% 25ppm 0805
R107,R112,R138|3|2k||||Resistor_SMD:R_0603_1608Metric||2k 0.1% 25ppm 0805
R108,R111,R142,R143,R145,R154,R155|7|3k||||Resistor_SMD:R_0603_1608Metric||3k 0.1% 25ppm 0805,3k 0603,3k 0805 0.1%
R109,R113|2|18k||||Resistor_SMD:R_0603_1608Metric||18k 0.1% 25ppm 0805
R114|1|72.3k||||Resistor_SMD:R_0603_1608Metric||72.3k 0.1% 25ppm 0805
R116|1|10R||||Resistor_SMD:R_0603_1608Metric||10 0.1% 25ppm 0805
R117|1|619k||||Resistor_SMD:R_0603_1608Metric||619k 0.1% 25ppm 0603
R118|1|150k||||Resistor_SMD:R_0603_1608Metric||150k 0.1% 25ppm 0603
R119,R153|2|100k||||Resistor_SMD:R_0603_1608Metric||100k,100k 0603
R139,R140|2|330R||||Resistor_SMD:R_0603_1608Metric||330R 0805
R141|1|500R||||Resistor_SMD:R_0603_1608Metric||500R 0603 0.1%
SW1|1|XRSn_button||||Button_Switch_SMD:SW_Push_SPST_NO_Alps_SKRK||Push button switch, generic, two pins
TP1,TP2,TP3,TP4,TP8,TP23,TP32,TP36,TP40,TP44,TP45,TP52,TP54,TP60,TP73,TP74,TP75,TP76,TP77,TP78,TP79|21|RCT-0C||||digikey-footprints:PROBE_PAD_0805||PC TEST POINT NATURAL
U1,U4|2|AD8334ACPZ||||AD8334ACPZ:QFN50P900X900X100-65N||
U2|1|DSC1001DI2-125.0000T||||DSC1001DI2-125.0000T:CDFN4_2P5X2_MCH||
U3|1|MAX14808ETK_||||MAX14808ETK_:QFN50P1000X1000X80-69N||
U5|1|F280025PNS||||F280025PNS:PQFP_025PNSR_TEX||
U6|1|REF3030||||Package_TO_SOT_SMD:SOT-23||3.0V 50-ppm/°C Max, 50-μA, CMOS Voltage Reference, SOT-23-3
U7|1|MIC920YC5-TR||||MIC920YC5-TR:SOT65P210X110-5N|Microchip|
U8,U9,U10,U11|4|TLV9354IDR||||TLV9354IDR:SOIC_9354IDR_TEX||
U12|1|TPS63700DRCR||||TPS63700DRCR:VREG_V62_16624-01YE||
U13|1|M24M01E-FMN6TP||||M24M01E-FMN6TP:SO8N_4X5X1P27_STM||
U14|1|LDL212PU50R||||LDL212PU50R:DFN_2PU50R_STM||
U15,U16|2|AZ1117CH2-3.3||||Package_TO_SOT_SMD:SOT-223-3_TabPin2||1A Fixed 3.3V LDO Linear Regulator, 15V Max Input, SOT-223
U17|1|TRS3221EIPWR||||TRS3221EIPWR:SOP65P640X120-16N||
U18,U19,U20|3|BZX84C3V3TS-7-F||||BZX84C3V3TS-7-F:SOT-363_DIO||
U22,U23|2|ESD7C3.3DT5G||||SOT_C3.3DT5G_ONS||
Y2|1|H130B-16.000-18-3030-EXT-TR||||KiCad:H130B16000183030EXTTR||MHz Crystal, 16 MHz, 5 x 3.2 mm, +/-30 ppm tolerance, +/-30 ppm stability, 18 pF, -40~85C, SMD

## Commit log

2025-11-30 first upload, 60% done
2025-12-04 finished pulser & mcu, receiver & power remaining
2025-12-09 converted diff signals to single-ended, modified pulser & MCU, power untouched
2025-12-15 finished analog signal chain, added main power components, complete the schematic and form a power budget table
2025-12-15 finished 50% of power section, 50% remaining + EEPROM & revision
2025-12-17 95% done, only headers for communication & power are remaining + RS232 transceiver & 1.5v reference
2025-12-17 DONE (inshallah)
2025-12-21 started layout, 20-30% done
2025-12-23 finished 70% of the layout, only power is remaining + matching parts with each other (analog)
2025-12-23 finished laying out all individual blocks, integration comes next, updated schematic
2025-12-25 fininshed 90% placement, only power section needs refinement, next sprint the stackup will be decided, probably 6 layers
2025-12-25 Finished placement & started routing, check on stackup & see routing & sigal integrity videos downloaded
2025-12-29 started routing, finished 15%
2025-12-29 finished power section, 70% AFE, re-think the stackup and the AFE stage near the MCU
2025-12-31 Finished 70% fr this time, power planes are remaining and some minor connections to the AFE's power & cfg pins, dont forget xrst
2026-01-01 1/4 AFE edits left to go, check if MCU ADC channels could be swapped (use oth ADCs), add voltage monitoring & power planes
2026-01-11 5% left, rearrange ADC channels for right AFE
2026-01-12 re-arranged ADC channels, add voltage monitoring and connect remaining nets
2026-01-13 added voltage monitoring, negative HV remaining & their routing + minimal editing
2026-01-14 finished routing YAY! only negative voltage monitoring & DRC & ERC are remaining
2026-01-15 did DRC, negative voltage monitoring & AI revision are remaining
2026-01-18 added test points & fuse
2026-02-01 DONE! Added ESD protection & finalized everything before, this thing is ready for production
2026-02-02 edited voltage sensing resistor values to give headroom
2026-03-03 Several finishing updates to fit stocks & changed SMA from SMD to THT, updated schematics too
2026-04-02 updated manufacturing files
2026-05-07 added SMA 3d models, cleaned folder and added system diagram to schematic
